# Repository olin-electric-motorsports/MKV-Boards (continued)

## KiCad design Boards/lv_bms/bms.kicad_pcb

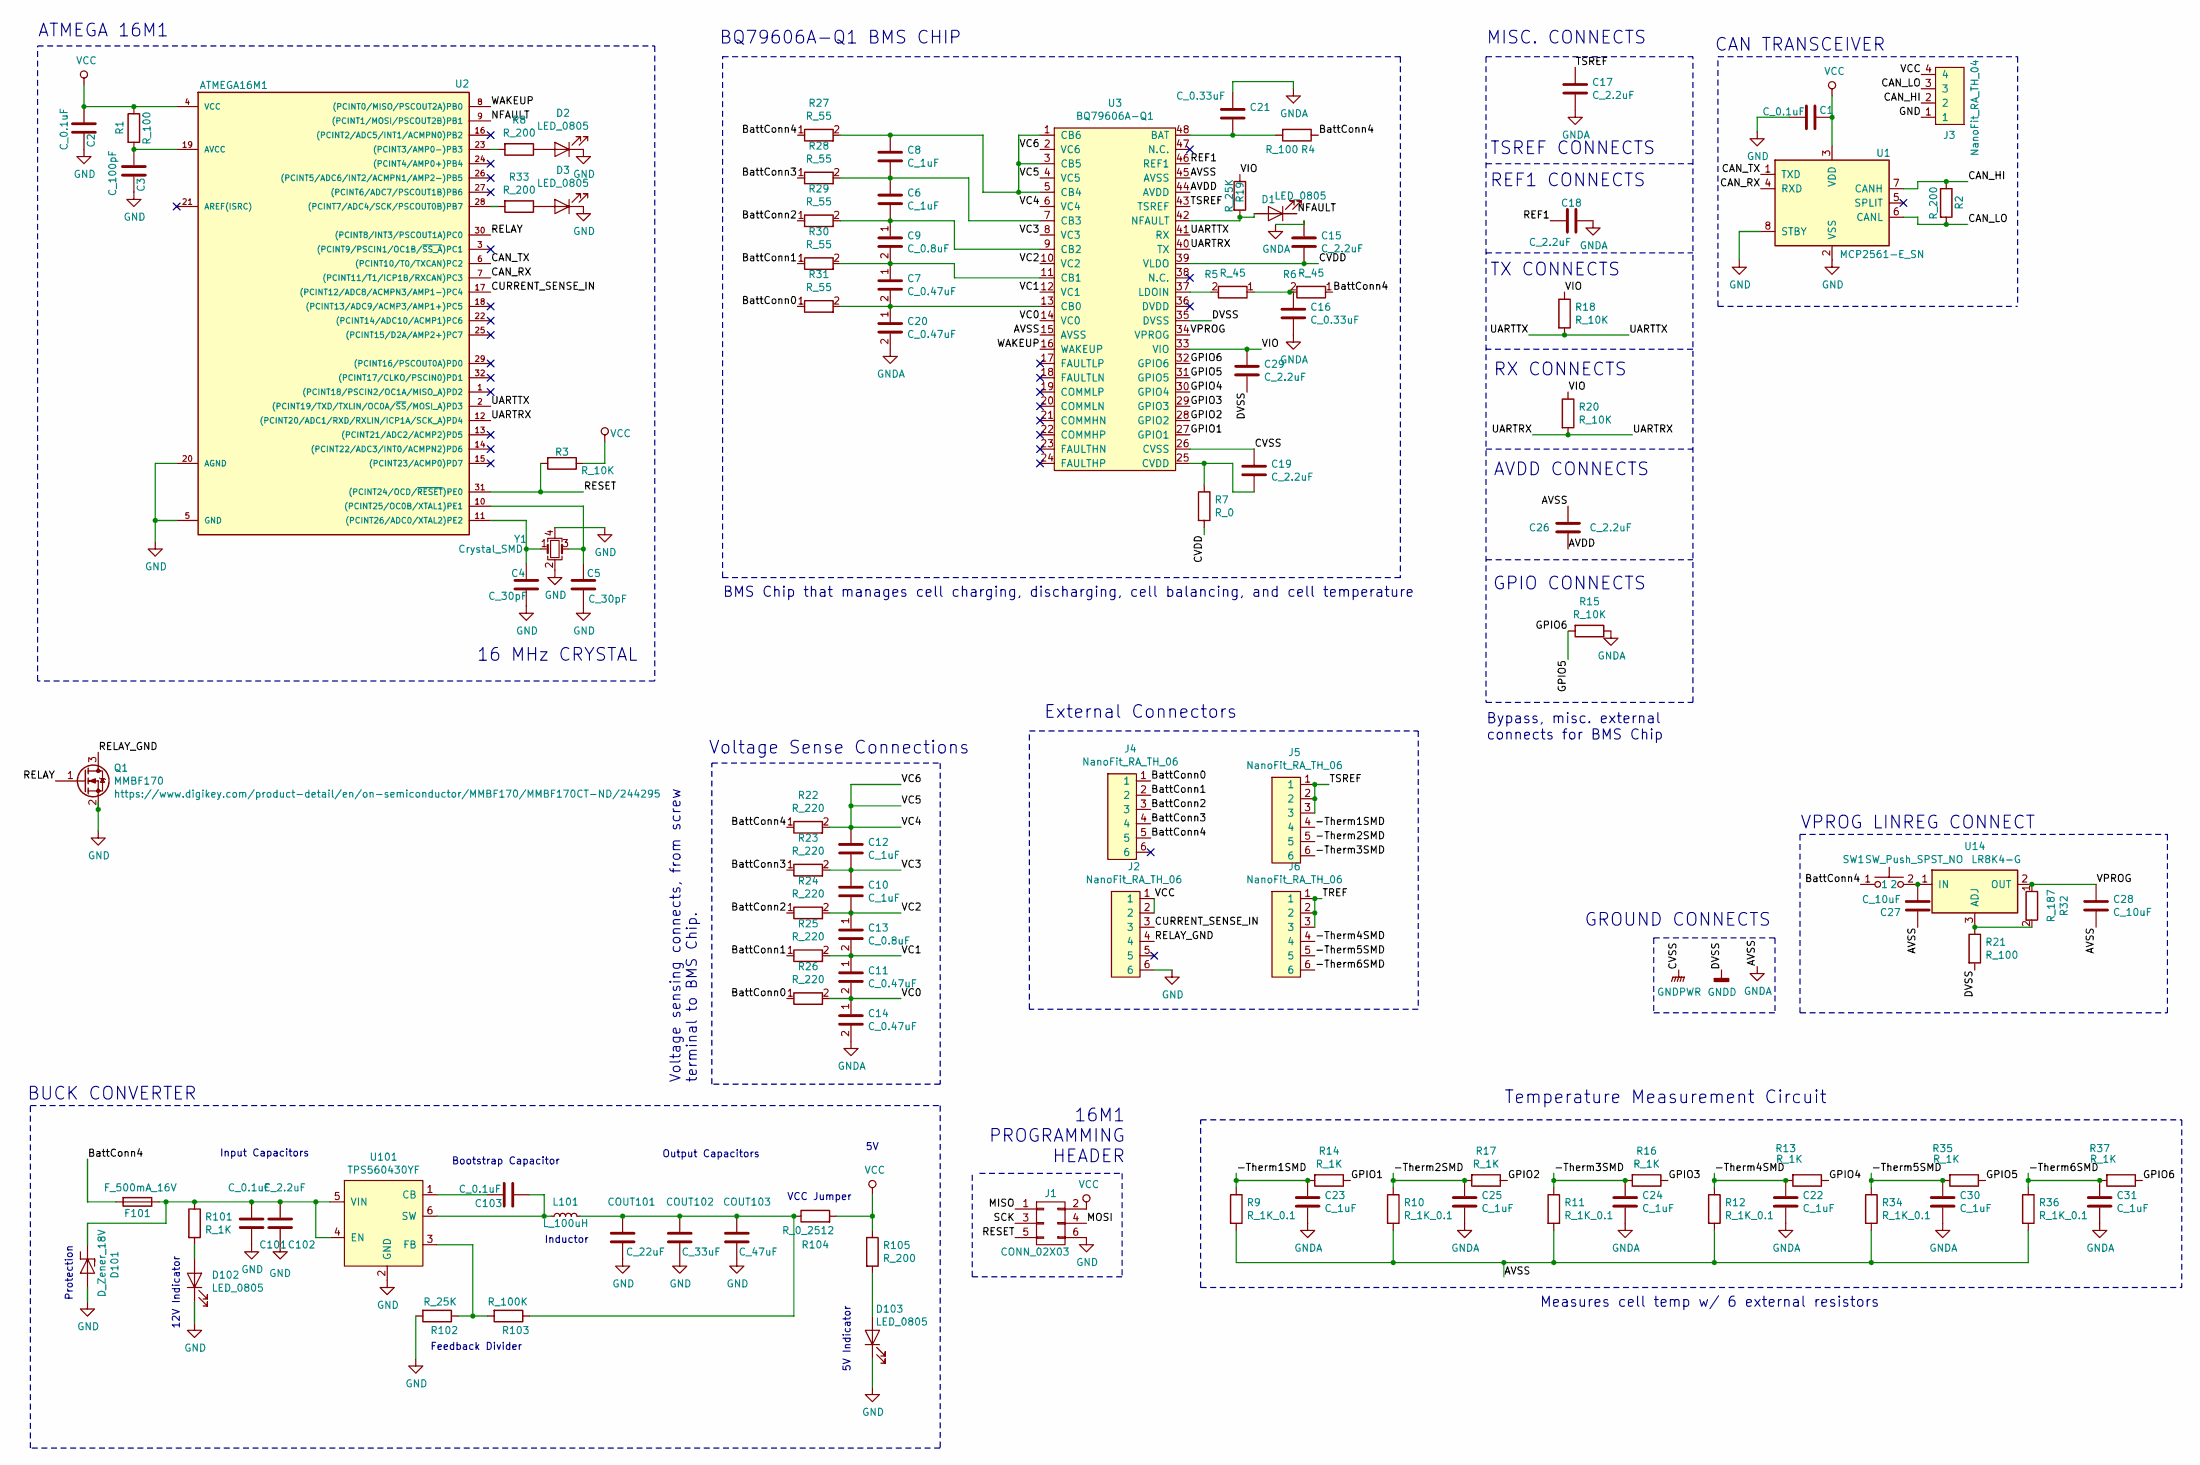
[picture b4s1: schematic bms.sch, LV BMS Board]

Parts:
C1, C2, C101, C103: C_0.1uF; C_0805_OEM; MPN 478-3352-1-ND
C3: C_100pF; C_0805_OEM; MPN 732-7852-1-ND
C4, C5: C_30pF; C_0805_OEM; MPN 1276-1130-1-ND
C6, C8, C10, C12, C22, C23, C24, C25, C30, C31: C_1uF; C_0805_OEM; MPN 1276-2887-1-ND
C7, C11, C14, C20: C_0.47uF; C_0805_OEM
C9, C13: C_0.8uF; C_0805_OEM
C15, C17, C18, C19, C26, C29, C102: C_2.2uF; C_0603_1608Metric; MPN 311-1451-1-ND
C16, C21: C_0.33uF; C_0805_OEM; MPN 478-5273-1-ND
C27, C28: C_10uF; C_0805_OEM; MPN 1276-1052-1-ND
COUT101: C_22uF; C_1206_OEM; MPN 445-11693-1-ND
COUT102: C_33uF; Fuse_1812; MPN 445-3924-1-ND
COUT103: C_47uF; C_0805_OEM; MPN 1276-6467-1-ND
D1, D2, D3, D102, D103: LED_0805; LED_0805_OEM; MPN 475-1410-1-ND
D101: D_Zener_18V; DO-214AA; MPN SMBJ5355B-TPMSCT-ND
F101: F_500mA_16V; Fuse_1210; MPN 507-1786-1-ND
J1: CONN_02X03; Pin_Header_Straight_2x03; MPN 609-3234-ND
J2, J4, J5, J6: NanoFit_RA_TH_06; NanoFit_RA_TH_6
J3: NanoFit_RA_TH_04; TerminalBlock_TE_282834-5_1x05_P2.54mm_Horizontal
L101: L_100uH; L_100uH_OEM; MPN 445-15759-1-ND
Q1: MMBF170; SOT-23-3_OEM; MPN MMBF170CT-ND
R1, R4: R_100; R_0805_OEM; MPN RNCP0805FTD100RCT-ND
R2, R105: R_200; R_0805_OEM; MPN RMCF0805JT200RCT-ND
R3: R_10K; R_0805_OEM; MPN CRS0805-FX-1002ELFCT-ND
R5, R6: R_45; R_0805_OEM
R7: R_0; R_0603_1608Metric; MPN P0.0GCT-ND
R8, R33: R_200; C_0805_OEM; MPN RMCF0805JT200RCT-ND
R9, R10, R11, R12, R34, R36: R_1K_0.1; C_0805_OEM; MPN P1.0KDACT-ND
R13, R14, R16, R17, R35, R37, R101: R_1K; C_0805_OEM; MPN RNCP0805FTD1K00CT-ND
R15, R18, R20: R_10K; C_0805_OEM; MPN CRS0805-FX-1002ELFCT-ND
R19: R_25K; C_0805_OEM; MPN A124124CT-ND
R21: R_100; C_0805_OEM; MPN RNCP0805FTD100RCT-ND
R22, R23, R24, R25, R26: R_220; C_0805_OEM
R27, R28, R29, R30, R31: R_55; C_0805_OEM
R32: R_187; C_0805_OEM
R102: R_25K; C_0805_OEM; Digi-key Part Number CPF-A-0805B25KE
R103: R_100K; C_0805_OEM; MPN P100KCCT-ND
R104: R_0_2512; R_2512_OEM; MPN A121322CT-ND
SW1: SW_Push_SPST_NO; SW_B3U-1000P_4.2x1.7mm; MPN SW1020CT-ND
U1: MCP2561-E_SN; SOIC-8_3.9x4.9mm_Pitch1.27mm_OEM; MPN MCP2561-E/SN-ND
U2: ATMEGA16M1; TQFP-32_7x7mm_Pitch0.8mm; MPN ATMEGA16M1-AU-ND
U3: BQ79606A-Q1; QFP50P900X900X120-48N
U14: LR8K4-G; TO-252-2; MPN 689-LR8K4-G
U101: TPS560430YF; SOT-23-6_OEM; MPN TPS560430YFDBVR
Y1: Crystal_SMD; Crystal_SMD_FA238; MPN 887-1125-1-ND

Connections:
/-Therm1SMD: C23.1, J5.4, R9.1, R14.2
/-Therm2SMD: C25.1, J5.5, R10.1, R17.2
/-Therm3SMD: C24.1, J5.6, R11.1, R16.2
/-Therm4SMD: C22.1, J6.4, R12.1, R13.2
/-Therm5SMD: C30.1, J6.5, R34.1, R35.2
/-Therm6SMD: C31.1, J6.6, R36.1, R37.2
/AVDD: C26.2, U3.44 (AVDD)
/BattConn0: J4.1, R26.1, R31.1
/BattConn1: J4.2, R25.1, R30.1
/BattConn2: J4.3, R24.1, R29.1
/BattConn3: J4.4, R23.1, R28.1
/BattConn4: F101.2, J4.5, R4.1, R6.1, R22.1, R27.1, SW1.1
/CAN_HI: J3.2, R2.1, U1.7 (CANH)
/CAN_LO: J3.3, R2.2, U1.6 (CANL)
/CAN_RX: U1.4 (RXD), U2.7 ((PCINT11/T1/ICP1B/RXCAN)PC3)
/CAN_TX: U1.1 (TXD), U2.6 ((PCINT10/T0/TXCAN)PC2)
/CURRENT_SENSE_IN: J2.3, U2.17 ((PCINT12/ADC8/ACMPN3/AMP1-)PC4)
/CVDD: C15.2, R7.2, U3.39 (VLDO)
/GPIO1: R14.1, U3.27 (GPIO1)
/GPIO2: R17.1, U3.28 (GPIO2)
/GPIO3: R16.1, U3.29 (GPIO3)
/GPIO4: R13.1, U3.30 (GPIO4)
/GPIO5: R15.2, R35.1, R37.1, U3.31 (GPIO5), U3.32 (GPIO6)
/MISO: J1.1
/MOSI: J1.4
/NFAULT: D1.1 (K), U2.9 ((PCINT1/MOSI/PSCOUT2B)PB1)
/REF1: C18.2, U3.46 (REF1)
/RELAY: Q1.1 (G), U2.30 ((PCINT8/INT3/PSCOUT1A)PC0)
/RELAY_GND: J2.4, Q1.3 (D)
/RESET: J1.5, R3.2, U2.31 ((PCINT24/OCD/~RESET~)PE0)
/SCK: J1.3
/TREF: J6.1, J6.2, J6.3
/TSREF: C17.2, J5.1, J5.2, J5.3, U3.43 (TSREF)
/UARTRX: R20.2, U2.12 ((PCINT20/ADC1/RXD/RXLIN/ICP1A/SCK_A)PD4), U3.40 (TX)
/UARTTX: R18.2, U2.2 ((PCINT19/TXD/TXLIN/OC0A/~SS~/MOSI_A)PD3), U3.41 (RX)
/VC0: C11.2, C14.1, R26.2, U3.14 (VC0)
/VC1: C11.1, C13.2, R25.2, U3.12 (VC1)
/VC2: C10.2, C13.1, R24.2, U3.10 (VC2)
/VC3: C10.1, C12.2, R23.2, U3.8 (VC3)
/VC4: C12.1, R22.2, U3.2 (VC6), U3.4 (VC5), U3.6 (VC4)
/VIO: C29.1, R18.1, R19.1, R20.1, U3.33 (VIO)
/VPROG: C28.1, R32.1, U3.34 (VPROG), U14.2 (OUT)
/WAKEUP: U2.8 ((PCINT0/MISO/PSCOUT2A)PB0), U3.16 (WAKEUP)
GND: C1.2, C2.2, C3.2, C4.2, C5.2, C101.2, C102.2, COUT101.2, COUT102.2, COUT103.2, D2.1 (K), D3.1 (K), D101.2 (A), D102.1 (K), D103.1 (K), J1.6, J2.6, J3.1, Q1.2 (S), R102.2, U1.2 (VSS), U1.8 (STBY), U2.5 (GND), U2.20 (AGND), U101.2 (GND), Y1.2, Y1.4
GNDA: C14.2, C15.1, C16.2, C17.1, C18.1, C20.2, C21.1, C22.2, C23.2, C24.2, C25.2, C26.1, C27.1, C28.2, C30.2, C31.2, R9.2, R10.2, R11.2, R12.2, R15.1, R34.2, R36.2, U3.15 (AVSS), U3.45 (AVSS)
GNDD: C29.2, R21.2, U3.35 (DVSS)
GNDPWR: C19.1, U3.26 (CVSS)
unnamed: C3.1, R1.2, U2.19 (AVCC)
unnamed: C4.1, U2.11 ((PCINT26/ADC0/XTAL2)PE2), Y1.1
unnamed: C5.1, U2.10 ((PCINT25/OC0B/XTAL1)PE1), Y1.3
unnamed: C6.1, C8.2, R28.2, U3.7 (CB3)
unnamed: C6.2, C9.1, R29.2, U3.9 (CB2)
unnamed: C7.1, C9.2, R30.2, U3.11 (CB1)
unnamed: C8.1, R27.2, U3.1 (CB6), U3.3 (CB5), U3.5 (CB4)
unnamed: C16.1, R5.1, R6.2
unnamed: C19.2, R7.1, U3.25 (CVDD)
unnamed: C7.2, C20.1, R31.2, U3.13 (CB0)
unnamed: C21.2, R4.2, U3.48 (BAT)
unnamed: C27.2, SW1.2, U14.1 (IN)
unnamed: C101.1, C102.1, D101.1 (K), F101.1, R101.1, U101.4 (EN), U101.5 (VIN)
unnamed: C103.1, U101.1 (CB)
unnamed: C103.2, L101.1, U101.6 (SW)
unnamed: COUT101.1, COUT102.1, COUT103.1, L101.2, R103.1, R104.1
unnamed: D1.2 (A), R19.2, U3.42 (NFAULT)
unnamed: D2.2 (A), R8.1
unnamed: D3.2 (A), R33.1
unnamed: D102.2 (A), R101.2
unnamed: D103.2 (A), R105.2
unnamed: R5.2, U3.37 (LDOIN)
unnamed: R8.2, U2.23 ((PCINT3/AMP0-)PB3)
unnamed: R21.1, R32.2, U14.3 (ADJ)
unnamed: R33.2, U2.28 ((PCINT7/ADC4/SCK/PSCOUT0B)PB7)
unnamed: R102.1, R103.2, U101.3 (FB)
VCC: C1.1, C2.1, J1.2, J2.1, J2.2, J3.4, R1.1, R3.1, R104.2, R105.1, U1.3 (VDD), U2.4 (VCC)

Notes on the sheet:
CAN TRANSCEIVER
ATMEGA 16M1
16 MHz CRYSTAL
16M1 PROGRAMMING HEADER
Voltage Sense Connections
Temperature Measurement Circuit
GPIO CONNECTS
TSREF CONNECTS
REF1 CONNECTS
Input Capacitors
12V Indicator
Protection
BUCK CONVERTER
Feedback Divider
Inductor
Bootstrap Capacitor
Output Capacitors
VCC Jumper
5V Indicator
GROUND CONNECTS
BQ79606A-Q1 BMS CHIP
TX CONNECTS
BMS Chip that manages cell charging, discharging, cell balancing, and cell temperature
Measures cell temp w/ 6 external resistors
MISC. CONNECTS
Voltage sensing connects, from screw terminal to BMS Chip.
Bypass, misc. external connects for BMS Chip
RX CONNECTS
AVDD CONNECTS
VPROG LINREG CONNECT
External Connectors

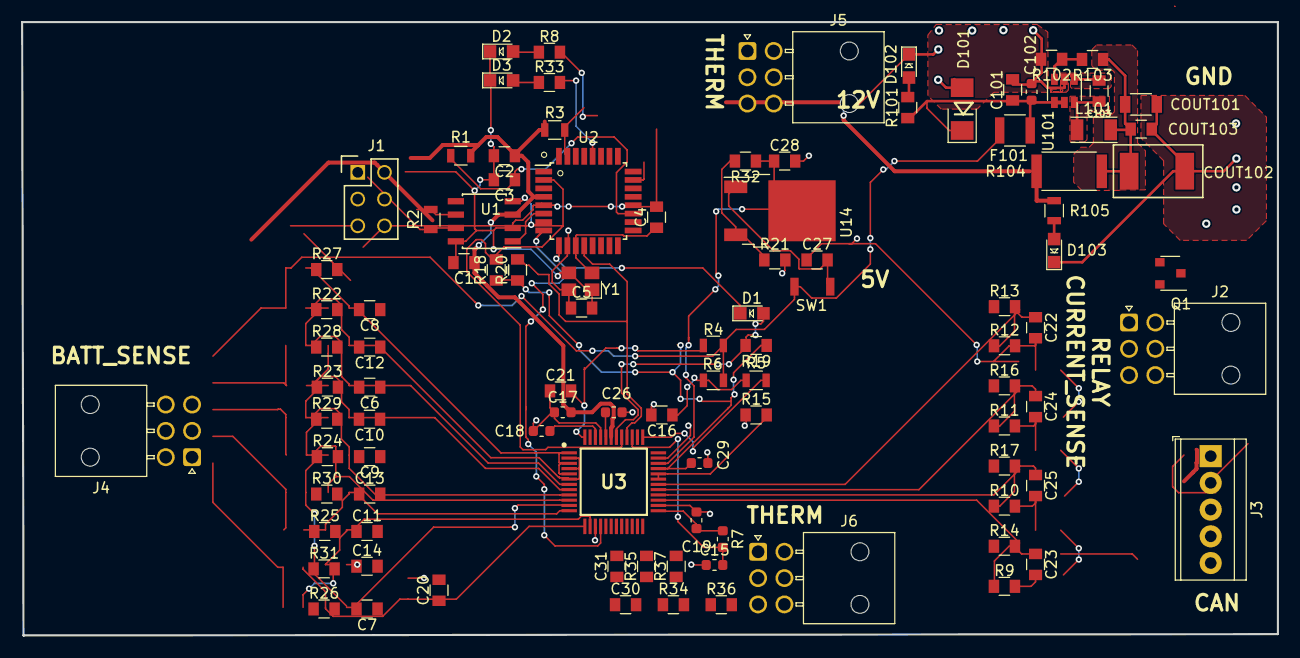
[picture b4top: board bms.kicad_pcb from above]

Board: 4 copper layers, 119.4 x 58.3 mm, 101 parts (0 on the bottom side), 71 nets.

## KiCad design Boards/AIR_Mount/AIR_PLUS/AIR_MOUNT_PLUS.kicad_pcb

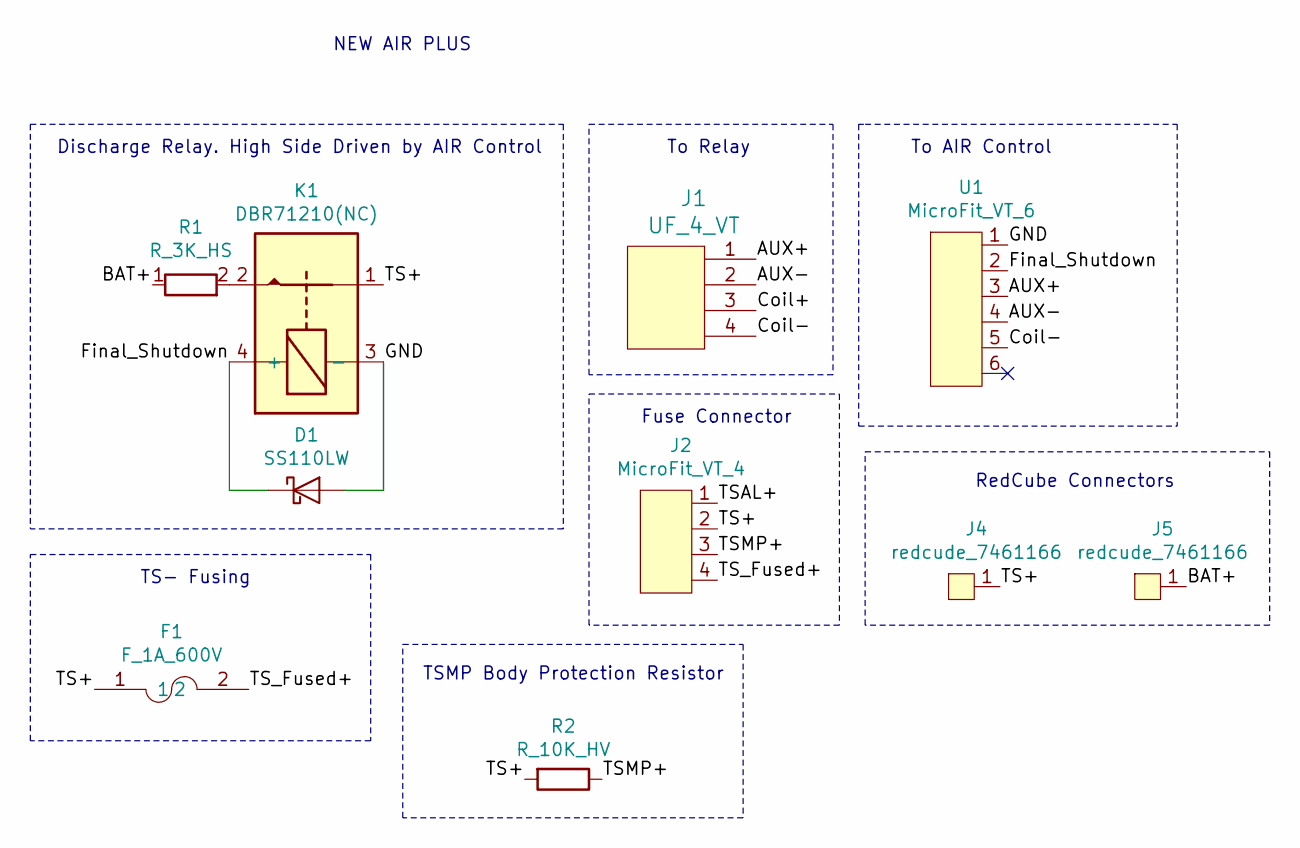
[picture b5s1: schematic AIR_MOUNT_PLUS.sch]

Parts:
D1: SS110LW; D_SOD-123W_OEM; MPN SS110LWRVGCT-ND
F1: F_1A_600V; Fuse_1A_600V
J1: UF_4_VT; Ultrafit_4; MPN WM11574-ND
J2: MicroFit_VT_4; MPN 430450414
J4, J5: redcude_7461166; redcube_7461166
K1: DBR71210(NC); D-Series_Cynergy_Relay; MPN 725-1049-ND
R1: R_3K_HS; R_3k_HS_TO247; MPN AP1013KJ-ND
R2: R_10K_HV; R_TSMP_SMD_5329; MPN PPC5D10.0KCT-ND
U1: MicroFit_VT_6; MPN 0430450614

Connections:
/AUX+: J1.1, U1.3
/AUX-: J1.2, U1.4
/BAT+: J5.1, R1.1
/Coil+: J1.3
/Coil-: J1.4, U1.5
/Final_Shutdown: D1.1 (K), K1.4 (+), U1.2
/GND: D1.2 (A), K1.3 (-), U1.1
/TS+: F1.1, J2.2, J4.1, K1.1, R2.2
/TSAL+: J2.1
/TSMP+: J2.3, R2.1
/TS_Fused+: F1.2, J2.4
unnamed: K1.2, R1.2

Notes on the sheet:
NEW AIR PLUS
Discharge Relay. High Side Driven by AIR Control
TS- Fusing
TSMP Body Protection Resistor
To Relay
To AIR Control
Fuse Connector
RedCube Connectors

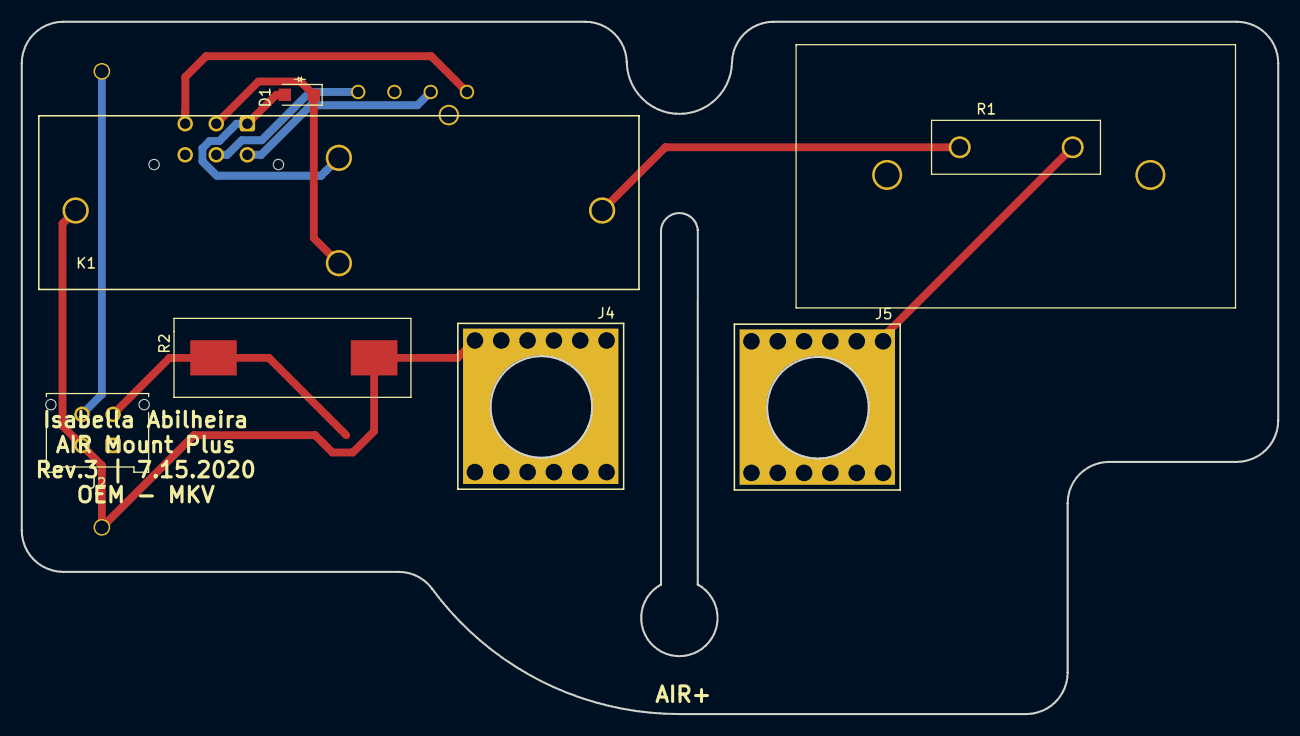
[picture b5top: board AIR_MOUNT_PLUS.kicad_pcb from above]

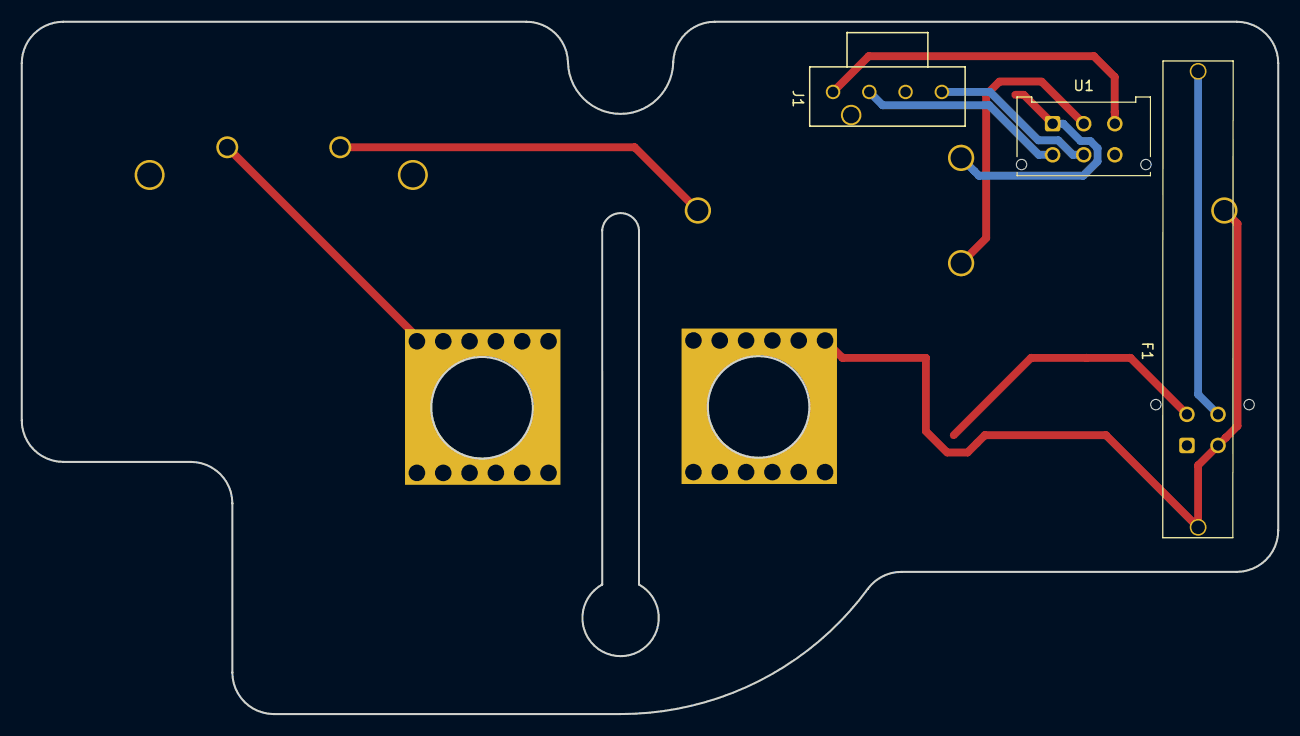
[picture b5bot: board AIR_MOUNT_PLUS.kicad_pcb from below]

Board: 2 copper layers, 121.2 x 66.8 mm, 10 parts (3 on the bottom side), 10 nets.

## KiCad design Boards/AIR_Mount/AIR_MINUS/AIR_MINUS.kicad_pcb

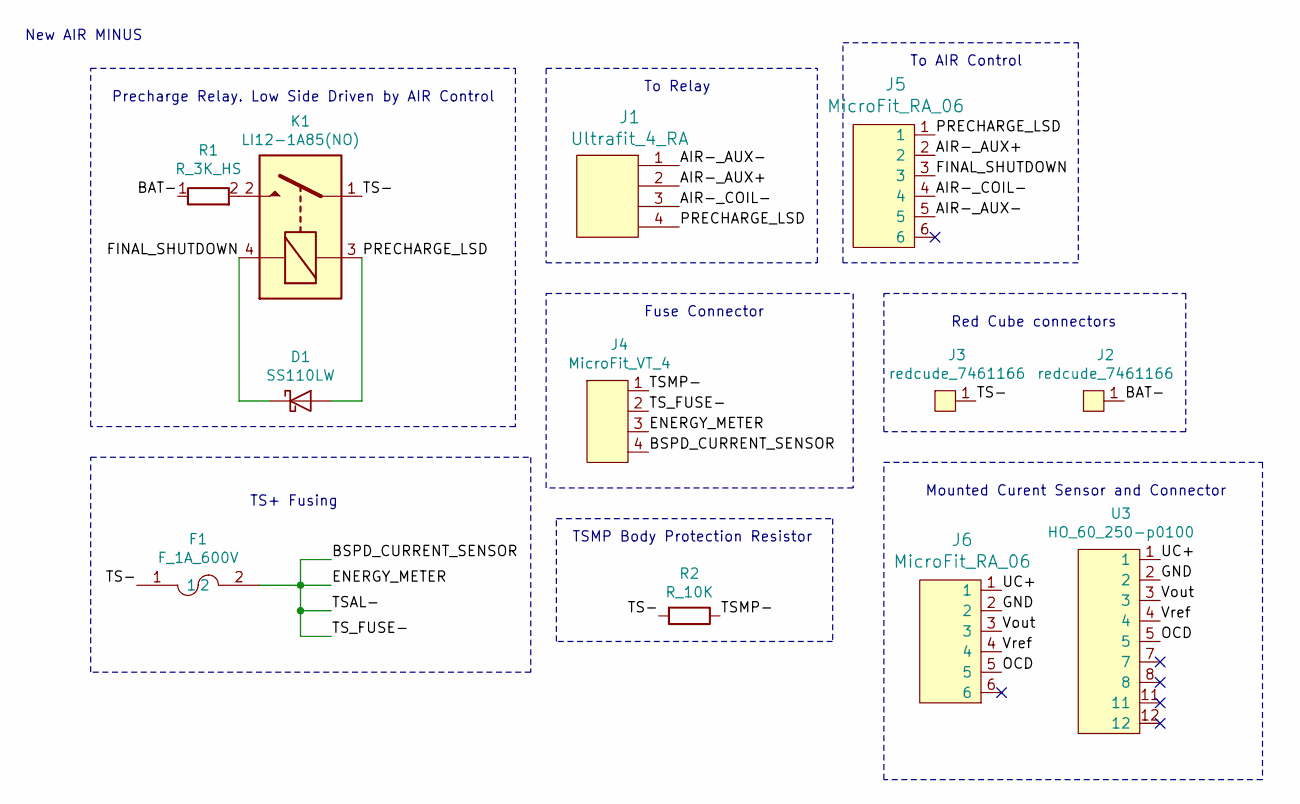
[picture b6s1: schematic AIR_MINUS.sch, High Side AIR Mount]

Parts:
D1: SS110LW; D_SOD-123W_OEM; MPN SS110LWRVGCT-ND
F1: F_1A_600V; Fuse_1A_600V
J1: Ultrafit_4_RA; MPN WM11574-ND
J2, J3: redcude_7461166; redcube_7461166
J4: MicroFit_VT_4; MPN 430450414
J5, J6: MicroFit_RA_06; MPN WM4037-ND
K1: LI12-1A85(NO); Meder-LI12; MPN 374-1110-ND
R1: R_3K_HS; R_3k_HS_TO247; MPN AP1013KJ-ND
R2: R_10K; R_TSMP_SMD_5329
U3: HO_60_250-p0100

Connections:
/AIR-_AUX+: J1.2, J5.2
/AIR-_AUX-: J1.1, J5.5
/AIR-_COIL-: J1.3, J5.4
/BAT-: J2.1, R1.1
/BSPD_CURRENT_SENSOR: F1.2, J4.2, J4.3, J4.4
/FINAL_SHUTDOWN: D1.1 (K), J5.3, K1.4
/GND: J6.2, U3.2
/OCD: J6.5, U3.5
/PRECHARGE_LSD: D1.2 (A), J1.4, J5.1, K1.3
/TS-: F1.1, J3.1, K1.1, R2.2
/TSMP-: J4.1, R2.1
/UC+: J6.1, U3.1
/Vout: J6.3, U3.3
/Vref: J6.4, U3.4
unnamed: K1.2, R1.2

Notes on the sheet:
TSMP Body Protection Resistor
TS+ Fusing
Precharge Relay. Low Side Driven by AIR Control
New AIR MINUS
Mounted Curent Sensor and Connector
Red Cube connectors
To Relay
Fuse Connector
To AIR Control

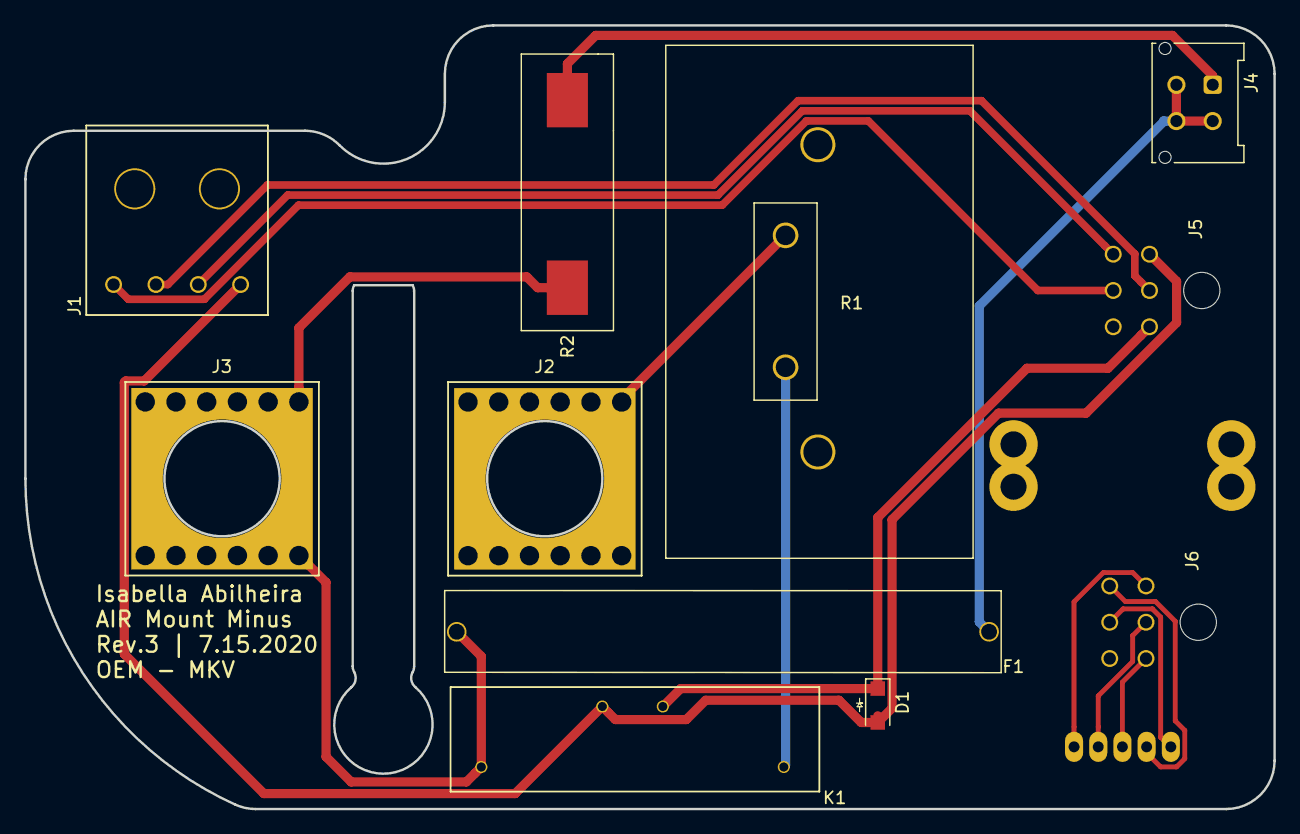
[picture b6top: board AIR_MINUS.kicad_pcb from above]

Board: 2 copper layers, 103.3 x 64.8 mm, 12 parts (1 on the bottom side), 15 nets.

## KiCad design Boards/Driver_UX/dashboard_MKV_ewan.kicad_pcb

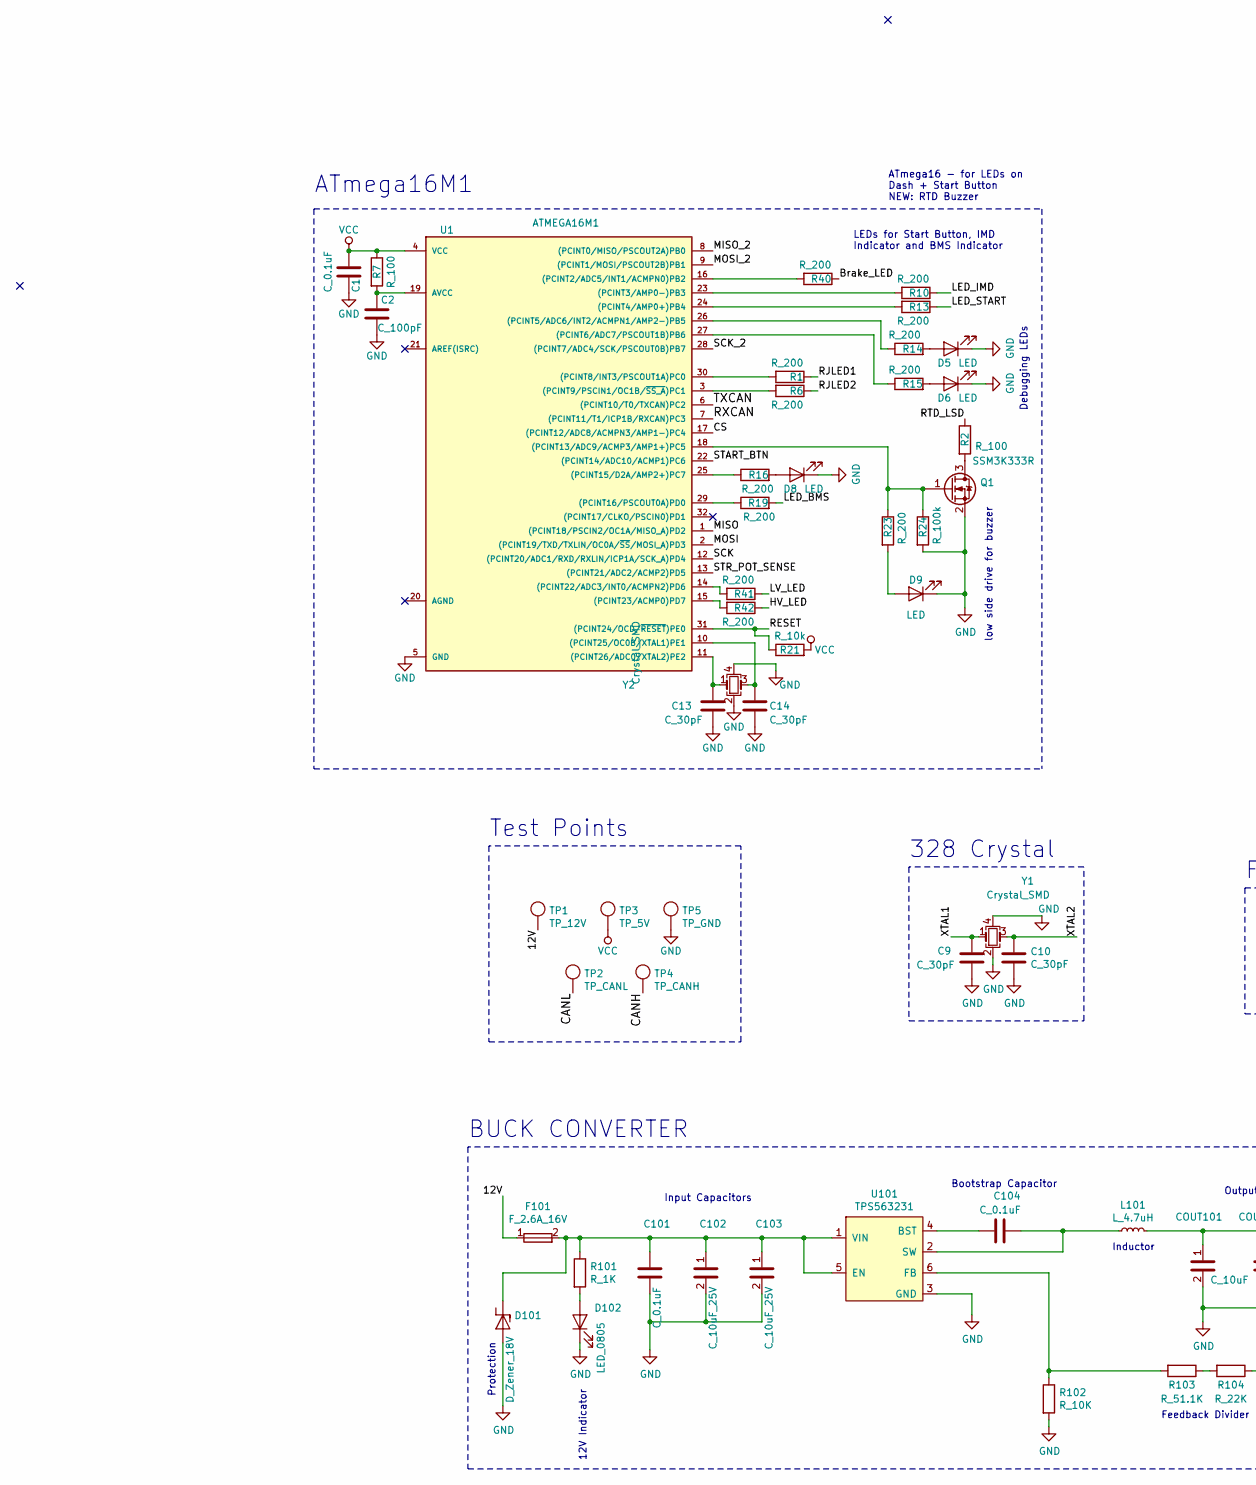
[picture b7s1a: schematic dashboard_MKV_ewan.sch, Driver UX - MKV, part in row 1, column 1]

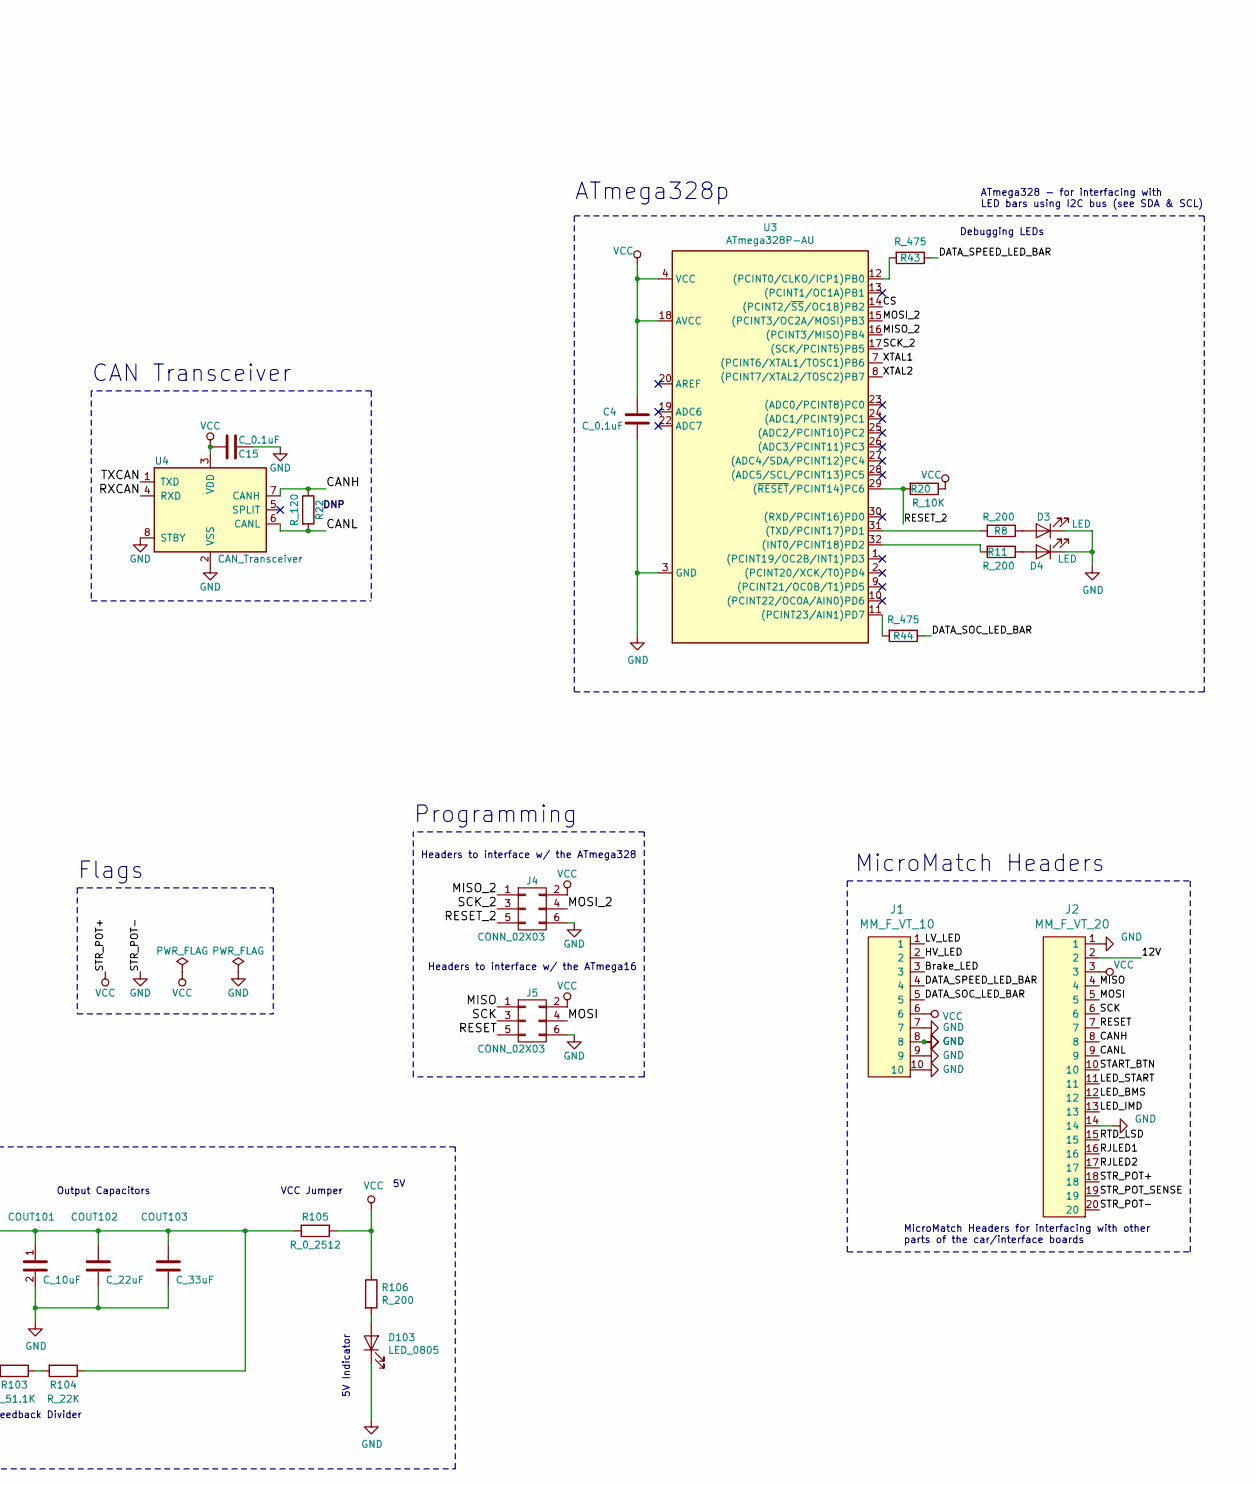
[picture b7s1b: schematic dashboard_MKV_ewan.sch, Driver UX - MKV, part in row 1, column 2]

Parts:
C1, C4, C15, C101, C104: C_0.1uF; C_0805_OEM; MPN 478-3352-1-ND
C2: C_100pF; C_0805_OEM; MPN 732-7852-1-ND
C9, C10, C13, C14: C_30pF; C_0805_OEM; MPN 1276-1130-1-ND
C102, C103: C_10uF_25V; C_0805_OEM
COUT101: C_10uF; C_0805_OEM
COUT102: C_22uF; C_1206_OEM; MPN 445-11693-1-ND
COUT103: C_33uF; C_1812_4532Metric; MPN 445-3924-1-ND
D3, D4, D5, D6, D8, D9: LED; LED_0805_OEM
D101: D_Zener_18V; DO-214AA; MPN SMBJ5355B-TPMSCT-ND
D102, D103: LED_0805; LED_0805_OEM; MPN 475-1410-1-ND
F101: F_2.6A_16V; Fuse_1812_4532Metric
J1: MM_F_VT_10; micromatch_female_vert_10; MPN 1-338068-0
J2: MM_F_VT_20; micromatch_female_vert_20; MPN 2-338068-0
J4, J5: CONN_02X03; Pin_Header_Straight_2x03; MPN 609-3234-ND
L101: L_4.7uH; IHLP2020BZER4R7M11-L_4.7_3.2A; MPN 445-6583-1-ND
Q1: SSM3K333R; SOT-23F; MPN SSM3K333RLFCT-ND
R1, R6, R8, R10, R11, R13, R14, R15, R16, R19, R40, R41, R42, R106: R_200; R_0805_OEM; MPN RMCF0805JT200RCT-ND
R2, R7: R_100; R_0805_OEM; MPN RNCP0805FTD100RCT-ND
R20, R102: R_10K; R_0805_OEM; MPN CRS0805-FX-1002ELFCT-ND
R21: R_10k; R_0805_OEM; MPN CRS0805-FX-1002ELFCT-ND
R22: R_120; R_0805_OEM; MPN RMCF0805JT200RCT-ND
R23: R_200; R_0805_OEM
R24: R_100k; R_0805_OEM
R43, R44: R_475; R_0805_OEM; MPN 311-475CRCT-ND
R101: R_1K; R_0805_OEM; MPN RNCP0805FTD1K00CT-ND
R103: R_51.1K; R_0805_OEM; MPN P51.1KCCT-ND
R104: R_22K; R_0805_OEM; MPN RMCF0805JT22K0CT-ND
R105: R_0_2512; R_2512_OEM; MPN A121322CT-ND
TP1: TP_12V; tp_1.6mm; MPN 36-5006-ND
TP2: TP_CANL; tp_1.6mm; MPN 36-5006-ND
TP3: TP_5V; tp_1.6mm; MPN 36-5006-ND
TP4: TP_CANH; tp_1.6mm; MPN 36-5006-ND
TP5: TP_GND; tp_1.6mm; MPN 36-5006-ND
U1: ATMEGA16M1; TQFP-32_7x7mm_Pitch0.8mm; MPN ATMEGA16M1-AU-ND
U3: ATmega328P-AU; TQFP-32_7x7mm_P0.8mm
U4: CAN_Transceiver; SOIC-8_3.9x4.9mm_Pitch1.27mm_OEM; MPN MCP2561-E/SN-ND
U101: TPS563231; SOT-563
Y1, Y2: Crystal_SMD; Crystal_SMD_FA238; MPN 887-1125-1-ND

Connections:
/12V: F101.1, J2.2, TP1.1
/Brake_LED: J1.3, R40.1
/CANH: J2.8, R22.1, TP4.1, U4.7 (CANH)
/CANL: J2.9, R22.2, TP2.1, U4.6 (CANL)
/CS: U1.17 ((PCINT12/ADC8/ACMPN3/AMP1-)PC4), U3.14 ((PCINT2/~SS~/OC1B)PB2)
/DATA_SOC_LED_BAR: J1.5, R44.1
/DATA_SPEED_LED_BAR: J1.4, R43.1
/HV_LED: J1.2, R42.1
/LED_BMS: J2.12, R19.2
/LED_IMD: J2.13, R10.1
/LED_START: J2.11, R13.1
/LV_LED: J1.1, R41.1
/MISO: J2.4, J5.1, U1.1 ((PCINT18/PSCIN2/OC1A/MISO_A)PD2)
/MISO_2: J4.1, U1.8 ((PCINT0/MISO/PSCOUT2A)PB0), U3.16 ((PCINT3/MISO)PB4)
/MOSI: J2.5, J5.4, U1.2 ((PCINT19/TXD/TXLIN/OC0A/~SS~/MOSI_A)PD3)
/MOSI_2: J4.4, U1.9 ((PCINT1/MOSI/PSCOUT2B)PB1), U3.15 ((PCINT3/OC2A/MOSI)PB3)
/RESET: J2.7, J5.5, R21.1, U1.31 ((PCINT24/OCD/~RESET~)PE0)
/RESET_2: J4.5, R20.2, U3.29 ((~RESET~/PCINT14)PC6)
/RJLED1: J2.16, R1.1
/RJLED2: J2.17, R6.1
/RTD_LSD: J2.15, R2.1
/RXCAN: U1.7 ((PCINT11/T1/ICP1B/RXCAN)PC3), U4.4 (RXD)
/SCK: J2.6, J5.3, U1.12 ((PCINT20/ADC1/RXD/RXLIN/ICP1A/SCK_A)PD4)
/SCK_2: J4.3, U1.28 ((PCINT7/ADC4/SCK/PSCOUT0B)PB7), U3.17 ((SCK/PCINT5)PB5)
/START_BTN: J2.10, U1.22 ((PCINT14/ADC10/ACMP1)PC6)
/STR_POT_SENSE: J2.19, U1.13 ((PCINT21/ADC2/ACMP2)PD5)
/TXCAN: U1.6 ((PCINT10/T0/TXCAN)PC2), U4.1 (TXD)
/XTAL1: C9.1, U3.7 ((PCINT6/XTAL1/TOSC1)PB6), Y1.1
/XTAL2: C10.1, U3.8 ((PCINT7/XTAL2/TOSC2)PB7), Y1.3
GND: C1.2, C2.2, C4.2, C9.2, C10.2, C13.2, C14.2, C15.2, C101.2, C102.2, C103.2, COUT101.2, COUT102.1, COUT103.2, D3.1 (K), D4.1 (K), D5.1 (K), D6.1 (K), D8.1 (K), D9.1 (K), D101.2 (A), D102.1 (K), D103.1 (K), J1.7, J1.8, J1.9, J1.10, J2.1, J2.14, J2.20, J4.6, J5.6, Q1.2 (S), R24.2, R102.2, TP5.1, U1.5 (GND), U3.3 (GND), U4.2 (VSS), U4.8 (STBY), U101.3 (GND), Y1.2, Y1.4, Y2.2, Y2.4
unnamed: C2.1, R7.2, U1.19 (AVCC)
unnamed: C13.1, U1.11 ((PCINT26/ADC0/XTAL2)PE2), Y2.1
unnamed: C14.1, U1.10 ((PCINT25/OC0B/XTAL1)PE1), Y2.3
unnamed: C101.1, C102.1, C103.1, D101.1 (K), F101.2, R101.1, U101.1 (VIN), U101.5 (EN)
unnamed: C104.1, L101.1, U101.2 (SW)
unnamed: C104.2, U101.4 (BST)
unnamed: COUT101.1, COUT102.2, COUT103.1, L101.2, R104.1, R105.2
unnamed: D3.2 (A), R8.1
unnamed: D4.2 (A), R11.1
unnamed: D5.2 (A), R14.2
unnamed: D6.2 (A), R15.2
unnamed: D8.2 (A), R16.2
unnamed: D9.2 (A), R23.2
unnamed: D102.2 (A), R101.2
unnamed: D103.2 (A), R106.2
unnamed: Q1.1 (G), R23.1, R24.1, U1.18 ((PCINT13/ADC9/ACMP3/AMP1+)PC5)
unnamed: Q1.3 (D), R2.2
unnamed: R1.2, U1.30 ((PCINT8/INT3/PSCOUT1A)PC0)
unnamed: R6.2, U1.3 ((PCINT9/PSCIN1/OC1B/~SS_A~)PC1)
unnamed: R8.2, U3.31 ((TXD/PCINT17)PD1)
unnamed: R10.2, U1.23 ((PCINT3/AMP0-)PB3)
unnamed: R11.2, U3.32 ((INT0/PCINT18)PD2)
unnamed: R13.2, U1.24 ((PCINT4/AMP0+)PB4)
unnamed: R14.1, U1.26 ((PCINT5/ADC6/INT2/ACMPN1/AMP2-)PB5)
unnamed: R15.1, U1.27 ((PCINT6/ADC7/PSCOUT1B)PB6)
unnamed: R16.1, U1.25 ((PCINT15/D2A/AMP2+)PC7)
unnamed: R19.1, U1.29 ((PCINT16/PSCOUT0A)PD0)
unnamed: R40.2, U1.16 ((PCINT2/ADC5/INT1/ACMPN0)PB2)
unnamed: R41.2, U1.14 ((PCINT22/ADC3/INT0/ACMPN2)PD6)
unnamed: R42.2, U1.15 ((PCINT23/ACMP0)PD7)
unnamed: R43.2, U3.12 ((PCINT0/CLKO/ICP1)PB0)
unnamed: R44.2, U3.11 ((PCINT23/AIN1)PD7)
unnamed: R102.1, R103.2, U101.6 (FB)
unnamed: R103.1, R104.2
VCC: C1.1, C4.1, C15.1, J1.6, J2.3, J2.18, J4.2, J5.2, R7.1, R20.1, R21.2, R105.1, R106.1, TP3.1, U1.4 (VCC), U3.4 (VCC), U3.18 (AVCC), U4.3 (VDD)

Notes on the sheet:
MicroMatch Headers for interfacing with other parts of the car/interface boards
ATmega16 - for LEDs on Dash + Start Button NEW: RTD Buzzer
Flags
Debugging LEDs
LEDs for Start Button, IMD Indicator and BMS Indicator
low side drive for buzzer
CAN Transceiver
DNP
Test Points
ATmega16M1
328 Crystal
ATmega328p
MicroMatch Headers
ATmega328 - for interfacing with LED bars using I2C bus (see SDA & SCL)
Headers to interface w/ the ATmega16
Programming
Headers to interface w/ the ATmega328
Feedback Divider
12V Indicator
Input Capacitors
BUCK CONVERTER
Bootstrap Capacitor
Output Capacitors
Inductor
VCC Jumper
5V Indicator
Protection
